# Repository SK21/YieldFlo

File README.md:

# YieldFlo

YieldFlo is a combine yield and moisture monitoring system that works alongside [AgOpenGPS](https://github.com/AgOpenGPS-Official/AgOpenGPS). A Windows desktop app records yield rate, moisture, and GPS position continuously while harvesting, and produces spatial yield maps and job reports — paired with open-source hardware that mounts on the combine's clean-grain elevator.

## How it works

- **YieldFlo module** (ESP32 or STM32F1 firmware) reads an optical grain-flow sensor on the clean-grain elevator, an optional capacitance moisture sensor, and an optional RPM sensor, then streams live readings to the PC over WiFi UDP, wired Ethernet UDP, or CAN bus.
- **AgOpenGPS** supplies GPS position and section on/off state over UDP on the same network.
- **YieldFlo (PC app)** combines both streams in real time, calculates yield, stores every point to a local SQLite database, renders a live color-coded yield map, and generates per-job reports and CSV exports.

## Repository layout

| Folder | Contents |
|---|---|
| [`YieldFlo/`](YieldFlo) | Main Windows Forms application (.NET) — the PC-side app |
| [`YieldFloApp/`](YieldFloApp) | Deployed/runnable build output (exe + resources) |
| [`Modules/ESP32/YieldFlo_ESP32`](Modules/ESP32/YieldFlo_ESP32) | Module firmware for ESP32 — WiFi/Ethernet/CAN, web-portal configuration, OTA updates |
| [`Modules/STM32F1/YieldFlo_STM32F1`](Modules/STM32F1/YieldFlo_STM32F1) | CAN-only module firmware for STM32F103 ("Blue Pill") — compile-time settings, no wireless |
| [`PCBs/YF1`](PCBs/YF1) | KiCad design for the main module board (sensor conditioning, CAN transceiver, etc.) |
| [`PCBs/Moisture1`](PCBs/Moisture1) | KiCad design for the moisture daughter board (ADS1115 + OEM capacitance sensor interface) |
| [`Tools/SensorSim`](Tools/SensorSim) | Arduino-based signal generator for bench-testing module firmware without a combine |
| [`ModuleSimulator/`](ModuleSimulator) | Windows app that emulates a module over the network, for testing the PC app without hardware |

Each `Modules/` folder has its own README with build instructions, pinouts, and protocol details — see the links above.

## Getting started

1. Extract a [release](../../releases) (or build `YieldFlo.sln`) and run `YieldFlo.exe` — no installer needed. Requires Windows 10/11 and .NET Framework 4.8.
2. Flash a module (ESP32 or STM32F1 — see the module READMEs) and wire it to the elevator/moisture sensors.
3. Run AgOpenGPS on the same PC or network.
4. In YieldFlo: set units, profile, crop, and header, then start a job.

Full instructions are in the in-app user manual (`Help` button, or [`YieldFlo/Help/YieldFlo User Manual.md`](YieldFlo/Help/YieldFlo%20User%20Manual.md)).

### Rebuilding the manual

`YieldFlo/Help/` holds the manual as `.md`, `.html` and `.pdf`. All three ship, so all three have to be kept in step — the `.md` and `.html` are edited by hand, and the `.pdf` is printed from the `.html` by headless Edge:

```
"C:\Program Files (x86)\Microsoft\Edge\Application\msedge.exe" ^
  --headless=new --disable-gpu --no-pdf-header-footer ^
  --print-to-pdf="YieldFlo User Manual.pdf" ^
  "file:///F:/path/to/YieldFlo/Help/YieldFlo User Manual.html"
```

`--no-pdf-header-footer` is what keeps the browser's own URL and page numbers off the pages. The HTML carries its own print CSS for page breaks, so nothing else needs setting. Chrome works identically — the PDF is produced by Chromium's Skia backend either way.

The build copies `Help/**` into `YieldFloApp/Help/`; that copy is output, not a second source to edit.

## Features

- Live main-screen gauges: yield rate, moisture, sensor status, area/total/average, work rate
- Color-coded live yield map (GMap.NET) with heading-up rotation and coverage tracking
- Profiles, crops, headers, and fields — reusable per-combine/per-crop configuration
- Two-point yield and moisture calibration workflows
- Job history with reports and CSV export (RateController-compatible)
- Imperial and metric units throughout
- Multi-language UI (English, German, French, Dutch, Polish, Hungarian, Lithuanian, Russian)
- CAN or WiFi/Ethernet module communication, selectable per install

## License

GPL-3.0 — see [`LICENSE`](LICENSE).

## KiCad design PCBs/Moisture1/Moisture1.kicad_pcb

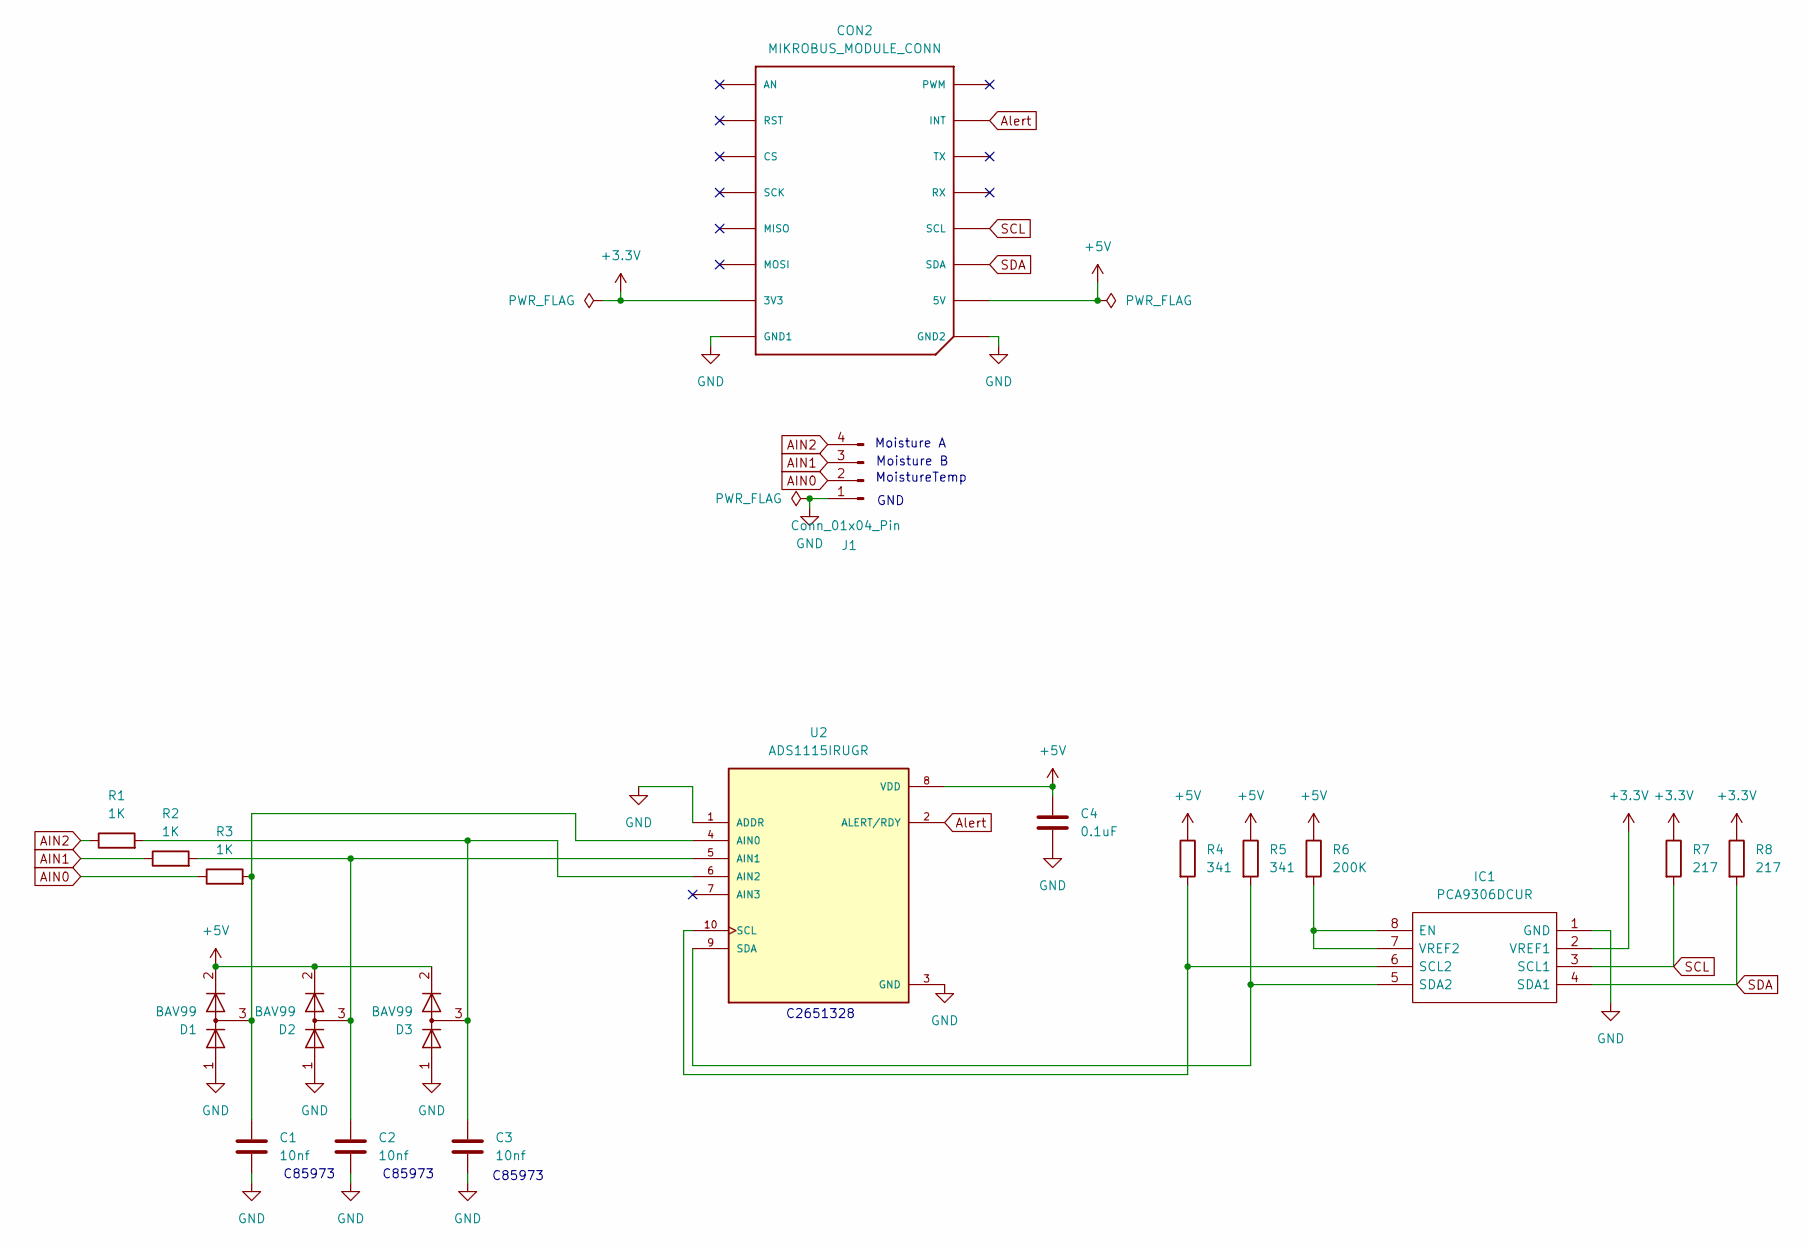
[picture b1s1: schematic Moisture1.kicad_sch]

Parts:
C1, C2, C3: 10nf; C_0603_1608Metric
C4: 0.1uF; C_0603_1608Metric
CON2: MIKROBUS_MODULE_CONN
D1, D2, D3: BAV99; SOT-23
IC1: PCA9306DCUR; Mouser Part Number 595-PCA9306DCUR
J1: Conn_01x04_Pin; PinHeader_1x04_P2.54mm_Vertical
R1, R2, R3: 1K; R_0603_1608Metric
R4, R5: 341; R_0603_1608Metric
R6: 200K; R_0603_1608Metric
R7, R8: 217; R_0603_1608Metric
U2: ADS1115IRUGR; IC_ADS1115IRUGR

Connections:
+3.3V: CON2.P7 (3V3), IC1.2 (VREF1), R7.1, R8.1
+5V: C4.1, CON2.P10 (5V), D1.2 (A), D2.2 (A), D3.2 (A), R4.1, R5.1, R6.1, U2.8 (VDD)
AIN0: J1.2, R3.1
AIN1: J1.3, R2.1
AIN2: J1.4, R1.1
Alert: CON2.P15 (INT), U2.2 (ALERT/RDY)
GND: C1.2, C2.2, C3.2, C4.2, CON2.P8 (GND1), CON2.P9 (GND2), D1.1 (K), D2.1 (K), D3.1 (K), IC1.1 (GND), J1.1, U2.1 (ADDR), U2.3 (GND)
unnamed: IC1.7 (VREF2), IC1.8 (EN), R6.2
unnamed: IC1.6 (SCL2), R4.2, U2.10 (SCL)
unnamed: IC1.5 (SDA2), R5.2, U2.9 (SDA)
unnamed: C1.1, D1.3 (K), R3.2, U2.4 (AIN0)
unnamed: C2.1, D2.3 (K), R2.2, U2.5 (AIN1)
unnamed: C3.1, D3.3 (K), R1.2, U2.6 (AIN2)
SCL: CON2.P12 (SCL), IC1.3 (SCL1), R7.2
SDA: CON2.P11 (SDA), IC1.4 (SDA1), R8.2

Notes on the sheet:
C85973
GND
C2651328
MoistureTemp
Moisture B
Moisture A

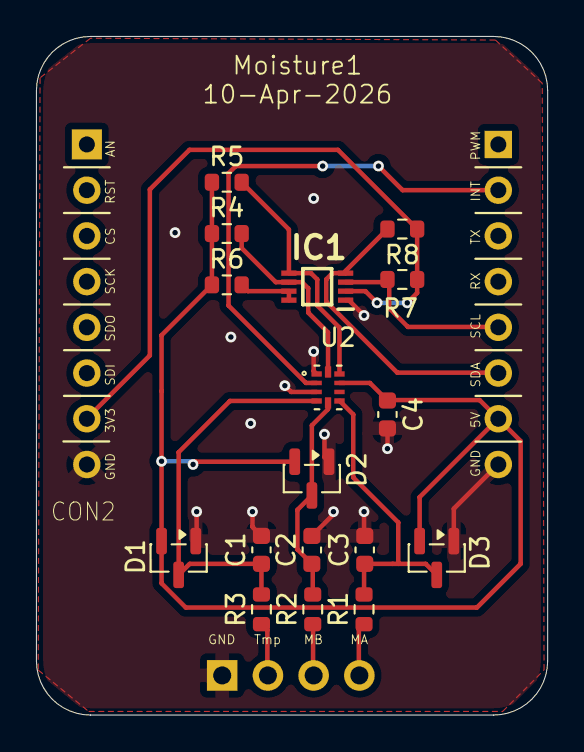
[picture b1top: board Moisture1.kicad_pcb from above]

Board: 2 copper layers, 28.4 x 37.7 mm, 19 parts (1 on the bottom side), 15 nets.

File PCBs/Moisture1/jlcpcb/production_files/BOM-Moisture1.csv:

Comment,Designator,Footprint,LCSC,Quantity
0.1uF,C4,C_0603_1608Metric,C14663,1
10nf,"C1,C2,C3",C_0603_1608Metric,C389113,3
1K,"R1,R2,R3",R_0603_1608Metric,C21190,3
200K,R6,R_0603_1608Metric,C25811,1
217,"R7,R8",R_0603_1608Metric,C2930075,2
341,"R4,R5",R_0603_1608Metric,C23138,2
ADS1115IRUGR,U2,IC_ADS1115IRUGR,C2651328,1
BAV99,"D1,D2,D3",SOT-23,C2500,3
PCA9306DCUR,IC1,PCA9306DCUR,C33196,1
MIKROBUS_MODULE_CONN,CON2,MIKROBUS_MODULE_CONN,,1
Conn_01x04_Pin,J1,PinHeader_1x04_P2.54mm_Vertical,,1

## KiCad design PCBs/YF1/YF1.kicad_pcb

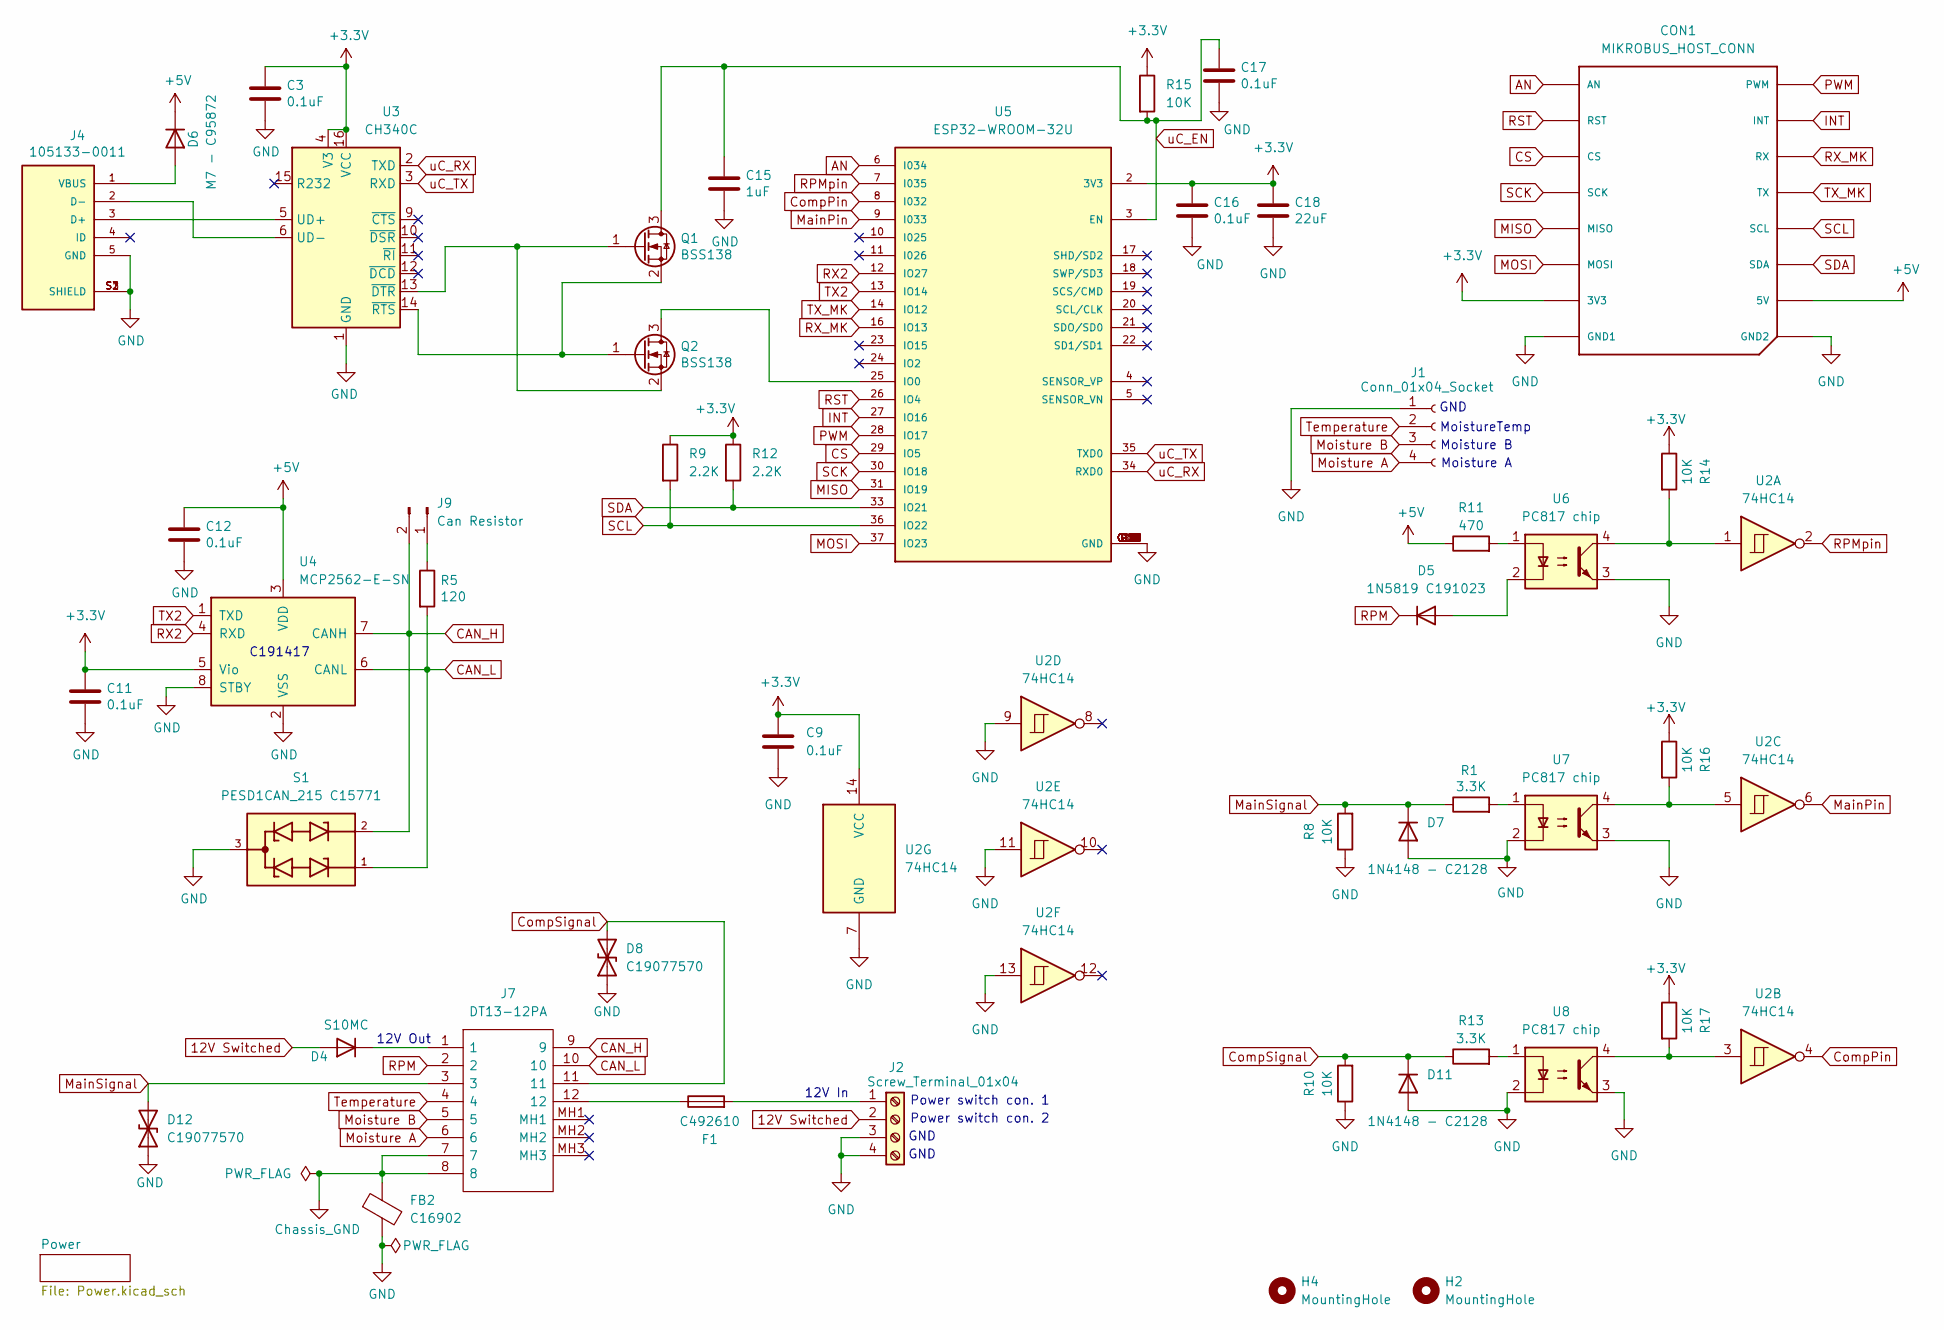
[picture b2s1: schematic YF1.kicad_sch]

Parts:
C3, C9, C11, C12, C16, C17: 0.1uF; C_0603_1608Metric
C15: 1uF; C_0603_1608Metric
C18: 22uF; C_0603_1608Metric
CON1: MIKROBUS_HOST_CONN
D4: S10MC; D_SMC_larger_pads
D5: 1N5819 C191023; 1N5819
D6: M7 - C95872; DO-214AC
D7, D11: 1N4148 - C2128; D_SOD-323
D8, D12: C19077570; D_SMB
F1: C492610; Fuse_Holder_C492610
FB2: C16902; D_1206_3216Metric
H2, H4: MountingHole; MountingHole_4.3mm_M4
J1: Conn_01x04_Socket; PinSocket_1x04_P2.54mm_Vertical
J2: Screw_Terminal_01x04; TerminalBlock_Phoenix_PT-1,5-4-5.0-H_1x04_P5.00mm_Horizontal
J4: 105133-0011; MOLEX_105133-0011; PARTREV C
J7: DT13-12PA; DT1312PA; Manufacturer_Part_Number DT13-12PA; Mouser Part Number 571-DT13-12PA
J9: Can Resistor; PinHeader_1x02_P2.54mm_Vertical
Q1, Q2: BSS138; SOT-23
R1, R13: 3.3K; R_0603_1608Metric
R5: 120; R_0603_1608Metric
R8, R10, R14, R15, R16, R17: 10K; R_0603_1608Metric
R9, R12: 2.2K; R_0603_1608Metric
R11: 470; R_0603_1608Metric
S1: PESD1CAN_215 C15771; DIO_PESD1CAN_215
U2: 74HC14; SOIC-14_3.9x8.7mm_P1.27mm
U3: CH340C; SOIC-16_3.9x9.9mm_P1.27mm
U4: MCP2562-E-SN; SOIC-8_3.9x4.9mm_P1.27mm
U5: ESP32-WROOM-32U; XCVR_ESP32-WROOM-32U; PARTREV V1.9
U6, U7, U8: PC817 chip; SMD-4_4.6x7.62mm_P2.54mm

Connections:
12V Switched: D4.2 (A), J2.2; also elsewhere on the board
+3.3V: C3.1, C9.1, C11.1, C16.1, C18.1, CON1.P7 (3V3), R9.1, R12.1, R14.1, R15.1, R16.1, R17.1, U2.14 (VCC), U3.4 (V3), U3.16 (VCC), U4.5 (Vio), U5.2 (3V3); also elsewhere on the board
+5V: C12.1, CON1.P10 (5V), D6.1 (K), R11.1, U4.3 (VDD); also elsewhere on the board
AN: CON1.P1 (AN), U5.6 (I034)
CAN_H: J7.9, J9.2, S1.2, U4.7 (CANH)
CAN_L: J7.10, R5.2, S1.1, U4.6 (CANL)
CS: CON1.P3 (CS), U5.29 (IO5)
Chassis_GND: FB2.1, J7.7, J7.8
CompPin: U2.4, U5.8 (I032)
CompSignal: D8.2 (A2), D11.1 (K), J7.11, R10.2, R13.1
GND: C3.2, C9.2, C11.2, C12.2, C15.2, C16.2, C17.2, C18.2, CON1.P8 (GND1), CON1.P9 (GND2), D7.2 (A), D8.1 (A1), D11.2 (A), D12.1 (A1), FB2.2, J1.1, J2.3, J2.4, J4.5 (GND), J4.S1 (SHIELD), J4.S2 (SHIELD), J4.S3 (SHIELD), R8.1, R10.1, S1.3, U2.7 (GND), U2.9, U2.11, U2.13, U3.1 (GND), U4.2 (VSS), U4.8 (STBY), U5.1 (GND), U5.15 (GND), U5.38 (GND), U5.G.1 (GND), U5.G.2 (GND), U5.G.4 (GND), U5.G.5 (GND), U5.G.6 (GND), U5.G.7 (GND), U5.G.8 (GND), U5.G.9 (GND), U5.G.10 (GND), U5.G.11 (GND), U5.G.12 (GND), U5.G.13 (GND), U5.G.14 (GND), U5.G.15 (GND), U5.G.16 (GND), U5.G.17 (GND), U5.G.18 (GND), U5.G.19 (GND), U5.G.20 (GND), U5.G.21 (GND), U5.G.22 (GND), U6.3, U7.2, U7.3, U8.2, U8.3; also elsewhere on the board
INT: CON1.P15 (INT), U5.27 (IO16)
MISO: CON1.P5 (MISO), U5.31 (IO19)
MOSI: CON1.P6 (MOSI), U5.37 (IO23)
MainPin: U2.6, U5.9 (I033)
MainSignal: D7.1 (K), D12.2 (A2), J7.3, R1.1, R8.2
Moisture A: J1.4, J7.6
Moisture B: J1.3, J7.5
unnamed: D4.1 (K), J7.1
unnamed: D5.2 (A), U6.2
unnamed: D6.2 (A), J4.1 (VBUS)
unnamed: F1.1, J7.12
unnamed: F1.2, J2.1
unnamed: J4.3 (D+), U3.5 (UD+)
unnamed: J4.2 (D-), U3.6 (UD-)
unnamed: J9.1, R5.1
unnamed: Q1.1 (G), Q2.2 (S), U3.13 (~DTR)
unnamed: Q1.2 (S), Q2.1 (G), U3.14 (~RTS)
unnamed: Q2.3 (D), U5.25 (IO0)
unnamed: R1.2, U7.1
unnamed: R11.2, U6.1
unnamed: R13.2, U8.1
unnamed: R14.2, U2.1, U6.4
unnamed: R16.2, U2.5, U7.4
unnamed: R17.2, U2.3, U8.4
PWM: CON1.P16 (PWM), U5.28 (IO17)
RPM: D5.1 (K), J7.2
RPMpin: U2.2, U5.7 (I035)
RST: CON1.P2 (RST), U5.26 (IO4)
RX2: U4.4 (RXD), U5.12 (IO27)
RX_MK: CON1.P14 (RX), U5.16 (IO13)
SCK: CON1.P4 (SCK), U5.30 (IO18)
SCL: CON1.P12 (SCL), R9.2, U5.36 (IO22)
SDA: CON1.P11 (SDA), R12.2, U5.33 (IO21)
TX2: U4.1 (TXD), U5.13 (IO14)
TX_MK: CON1.P13 (TX), U5.14 (IO12)
Temperature: J1.2, J7.4
uC_EN: C15.1, C17.1, Q1.3 (D), R15.2, U5.3 (EN)
uC_RX: U3.2 (TXD), U5.34 (RXD0)
uC_TX: U3.3 (RXD), U5.35 (TXD0)

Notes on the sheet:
Moisture A
12V Out
GND
MoistureTemp
12V In
Power switch con. 1
Power switch con. 2
C191417
Moisture B

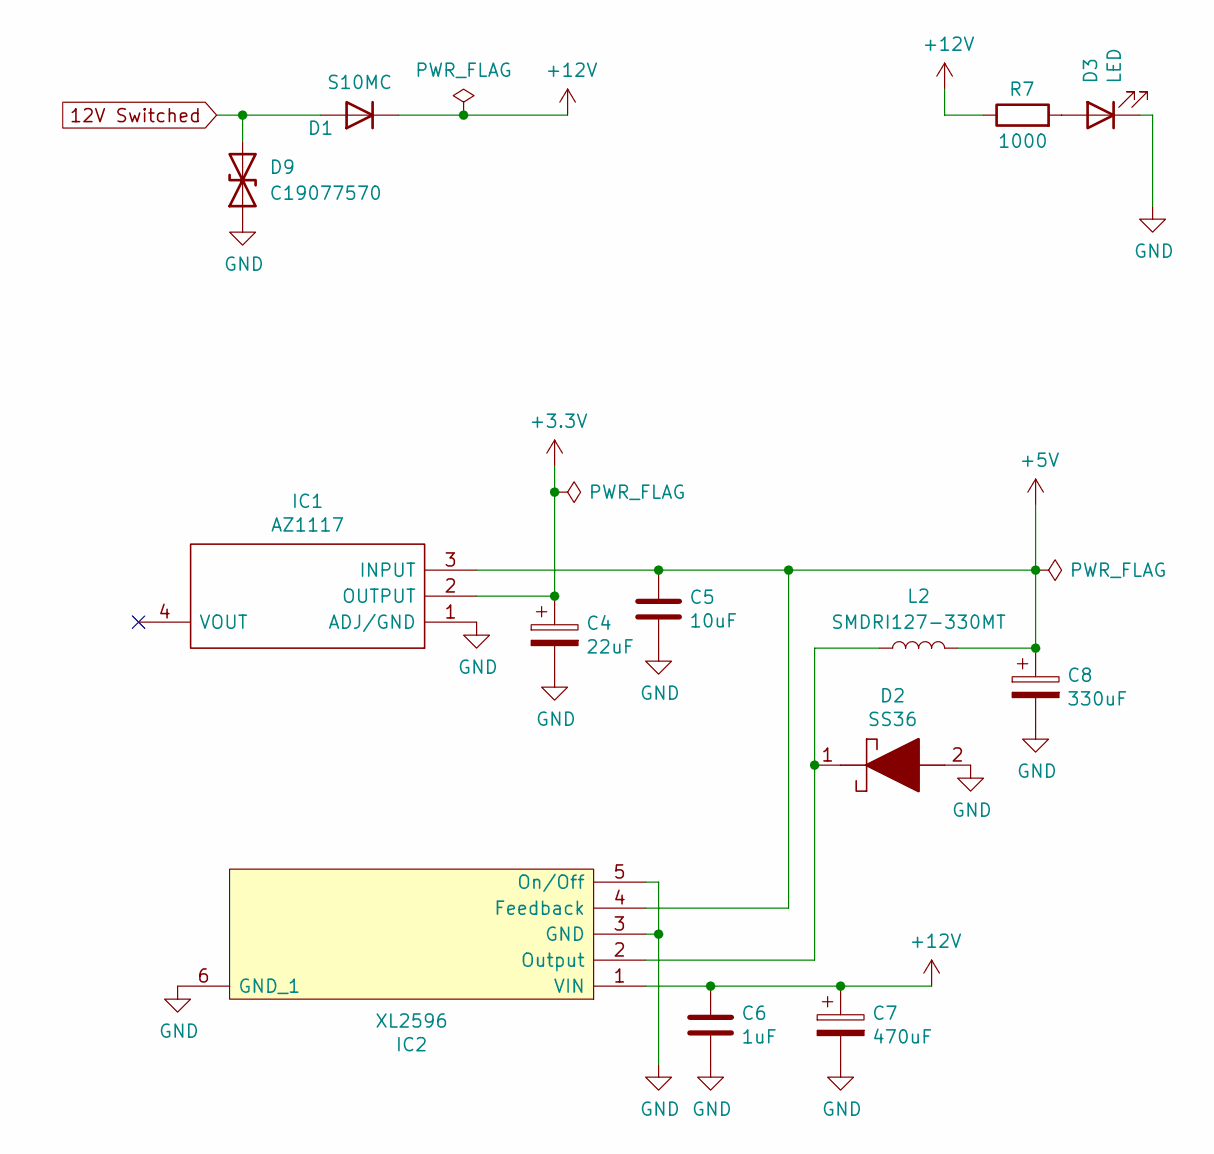
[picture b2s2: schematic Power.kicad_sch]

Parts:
C4: 22uF; C_0603_1608Metric
C5: 10uF; C_0603_1608Metric
C6: 1uF; C_0603_1608Metric
C7: 470uF; CP_Elec_10x10.5
C8: 330uF; CP_Elec_10x10.5
D1: S10MC; D_SMC_larger_pads
D2: SS36; SMA(DO-214AC)
D3: LED; LED_0805_2012Metric
D9: C19077570; D_SMB
IC1: AZ1117; SOT-223
IC2: XL2596; TO263-5L
L2: SMDRI127-330MT; TMPA1265SP-101MN-D
R7: 1000; R_0603_1608Metric

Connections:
12V Switched: D1.2 (A), D9.2 (A2); also elsewhere on the board
+3.3V: C4.1, IC1.2 (OUTPUT); also elsewhere on the board
+5V: C5.1, C8.1, IC1.3 (INPUT), IC2.4 (Feedback), L2.2; also elsewhere on the board
+12V: C6.1, C7.1, D1.1 (K), IC2.1 (VIN), R7.1
GND: C4.2, C5.2, C6.2, C7.2, C8.2, D2.2, D3.1 (K), D9.1 (A1), IC1.1 (ADJ/GND), IC2.3 (GND), IC2.5 (On/Off), IC2.6 (GND_1); also elsewhere on the board
unnamed: D3.2 (A), R7.2
unnamed: D2.1, IC2.2 (Output), L2.1

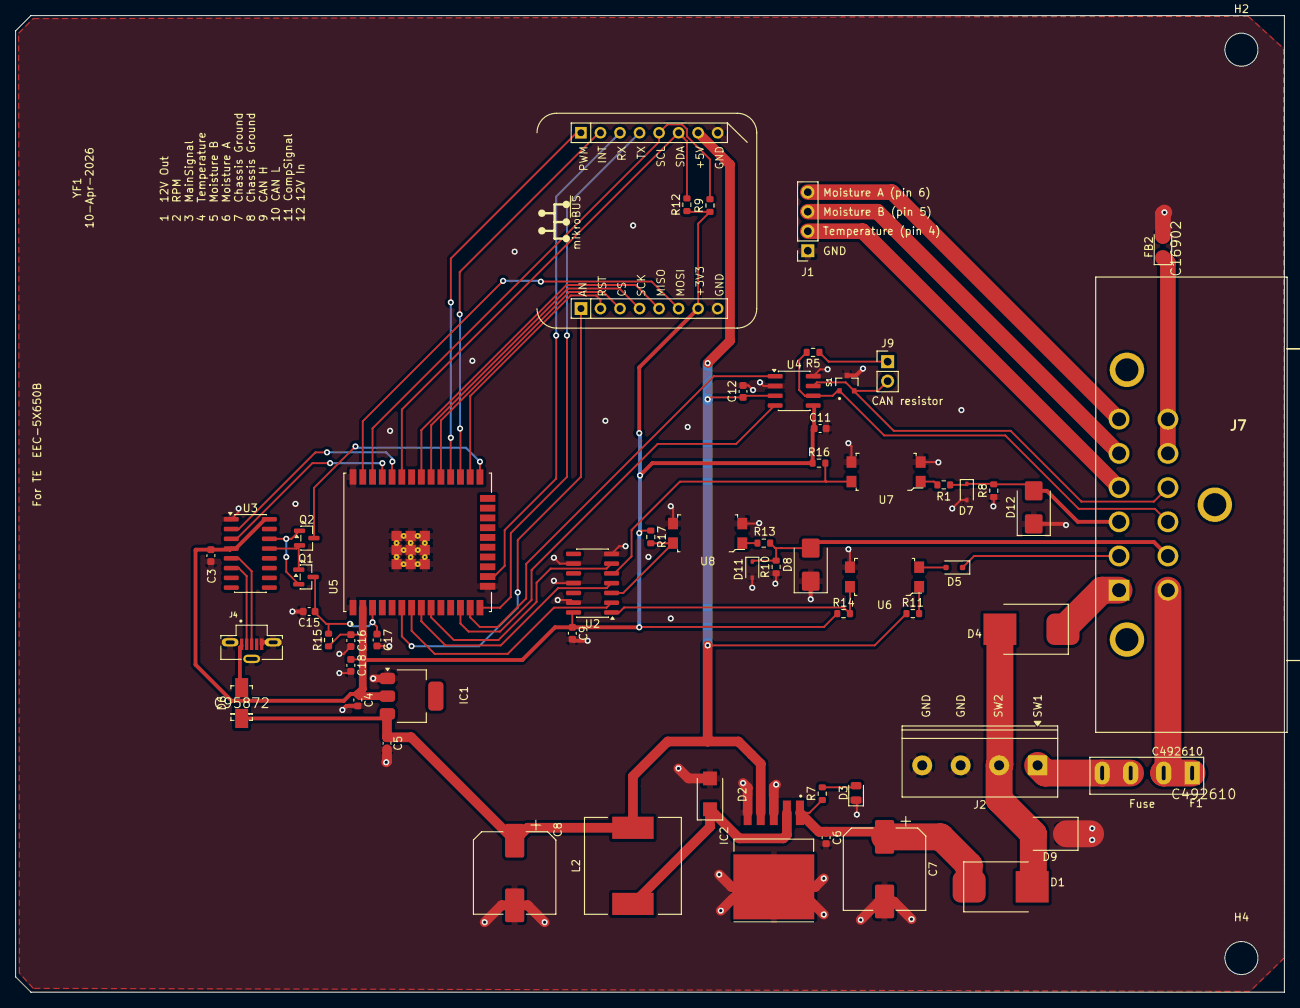
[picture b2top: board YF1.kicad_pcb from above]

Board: 2 copper layers, 165.0 x 127.0 mm, 60 parts (0 on the bottom side), 53 nets.

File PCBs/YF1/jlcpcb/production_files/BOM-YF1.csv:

Comment,Designator,Footprint,LCSC,Quantity
0.1uF,"C11,C12,C16,C17,C3,C9",C_0603_1608Metric,C14663,6
1000,R7,R_0603_1608Metric,C21190,1
105133-0011,J4,MOLEX_105133-0011,C586226,1
10K,"R10,R14,R15,R16,R17,R8",R_0603_1608Metric,C25804,6
10uF,C5,C_0603_1608Metric,C96446,1
120,R5,R_0603_1608Metric,C22787,1
1N4148 - C2128,"D11,D7",D_SOD-323,C2128,2
1N5819  C191023,D5,1N5819,C191023,1
1uF,"C15,C6",C_0603_1608Metric,C5199872,2
2.2K,"R12,R9",R_0603_1608Metric,C4190,2
22uF,"C18,C4",C_0603_1608Metric,C59461,2
3.3K,"R1,R13",R_0603_1608Metric,C2907023,2
330uF,C8,CP_Elec_10x10.5,C3032175,1
470,R11,R_0603_1608Metric,C114669,1
470uF,C7,CP_Elec_10x10.5,C2992611,1
74HC14,U2,SOIC-14_3.9x8.7mm_P1.27mm,C5605,1
AZ1117,IC1,SOT-223,C92102,1
BSS138,"Q1,Q2",SOT-23,C255592,2
C16902,FB2,D_1206_3216Metric,C16902,1
C19077570,"D12,D8,D9",D_SMB,C19077570,3
C492610,F1,Fuse_Holder_C492610,C492610,1
CH340C,U3,SOIC-16_3.9x9.9mm_P1.27mm,C84681,1
Can Resistor,J9,PinHeader_1x02_P2.54mm_Vertical,C7494857,1
Conn_01x04_Socket,J1,PinSocket_1x04_P2.54mm_Vertical,C2718488,1
ESP32-WROOM-32U,U5,XCVR_ESP32-WROOM-32U,C701344,1
LED,D3,LED_0805_2012Metric,C84256,1
M7 - C95872,D6,DO-214AC,C95872,1
MCP2562-E-SN,U4,SOIC-8_3.9x4.9mm_P1.27mm,C53609,1
PC817 chip,"U6,U7,U8",SMD-4_4.6x7.62mm_P2.54mm,C66405,3
PESD1CAN_215  C15771,S1,DIO_PESD1CAN_215,C15771,1
S10MC,"D1,D4",D_SMC_larger_pads,C169472,2
SMDRI127-330MT,L2,TMPA1265SP-101MN-D,C9400,1
SS36,D2,SMA(DO-214AC),C2903825,1
Screw_Terminal_01x04,J2,"TerminalBlock_Phoenix_PT-1,5-4-5.0-H_1x04_P5.00mm_Horizontal",C717432,1
XL2596,IC2,TO263-5L,C74190,1

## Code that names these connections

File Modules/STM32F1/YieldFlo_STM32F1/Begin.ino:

void DoSetup()
{
	uint8_t ErrorCount = 0;
	Serial.begin(38400);
	delay(2000);
	Serial.println();
	Serial.println();
	Serial.println(InoDescription);
	Serial.println();

	// version
	uint16_t yr = InoID % 10 + 2020;
	uint16_t rest = InoID / 10;
	uint8_t mn = rest % 100;
	uint16_t dy = rest / 100;

	String fwVer;
	if (mn <= 12 && dy <= 31)
	{
		fwVer = "Firmware Version: v";
		fwVer += String(yr);
		fwVer += ".";
		if (mn < 10) fwVer += "0";
		fwVer += String(mn);
		fwVer += ".";
		if (dy < 10) fwVer += "0";
		fwVer += String(dy);
	}
	else
	{
		fwVer = "Firmware Version: invalid";
	}
	Serial.println(fwVer);

	Serial.print("Module ID: ");
	Serial.println(ModuleID);
	Serial.println("");

	CheckExtiConflicts();

	// I2C
	Wire.begin();			// I2C1 on pins SCL PB6, SDA PB7
	Wire.setClock(400000);	// Increase I2C data rate to 400kHz

	// ADS1115
	if (ADS1115Enabled)
	{
		Serial.print("Starting ADS1115 at address ");
		Serial.println(ADS1115_Address);
		while (!ADSfound)
		{
			Wire.beginTransmission(ADS1115_Address);
			Wire.write(0b00000000);	//Point to Conversion register
			Wire.endTransmission();
			ADSfound = (Wire.requestFrom(ADS1115_Address, 2) == 2);
			Serial.print(".");
			delay(500);
			if (ErrorCount++ > 10) break;
		}
		Serial.println("");
		if (ADSfound)
		{
			Serial.println("ADS1115 found.");
			Serial.println("");

			// Configure ALERT/RDY pin for conversion-ready mode:
			// Set Hi_thresh MSB=1 and Lo_thresh MSB=0 — this puts ALERT/RDY
			// into conversion-ready mode regardless of comparator settings.
			Wire.beginTransmission(ADS1115_Address);
			Wire.write(0x02);		// Hi_thresh register
			Wire.write(0x80);		// 0x8000 MSB
			Wire.write(0x00);
			Wire.endTransmission();

			Wire.beginTransmission(ADS1115_Address);
			Wire.write(0x03);		// Lo_thresh register
			Wire.write(0x00);		// 0x0000
			Wire.write(0x00);
			Wire.endTransmission();

			// Attach interrupt — ALERT/RDY is open-drain active-low
			pinMode(AlertPin, INPUT_PULLUP);
			attachInterrupt(digitalPinToInterrupt(AlertPin), onADSReady, FALLING);

			// Start first conversion — moisture (AIN0-AIN1 differential, PGA=±4.096V, 16 SPS)
			Wire.beginTransmission(ADS1115_Address);
			Wire.write(0x01);		// Config register
			Wire.write(0b10000011);	// OS=1, MUX=000 (AIN0-AIN1 diff), PGA=001 (4.096V), MODE=1
			Wire.write(0b00100000);	// DR=001 (16 SPS), COMP_QUE=00
			Wire.endTransmission();
		}
		else
		{
			Serial.println("ADS1115 not found.");
			Serial.println("ADS1115 disabled.");
			Serial.println("");
		}
	}

	// Optical sensor
	Serial.print("Starting optical sensor ... ");
	pinMode(MainPin, INPUT);
	attachInterrupt(digitalPinToInterrupt(MainPin), onSensorEdge, CHANGE);
	if (UseCompSignal)
	{
		pinMode(CompPin, INPUT);
		attachInterrupt(digitalPinToInterrupt(CompPin), onSensorEdge, CHANGE);
	}
	BeamBlocked = ((digitalRead(MainPin) == HIGH) == InvertSensor);	// PNP: HIGH = clear; NPN inverted
	LastEdgeUs = micros();
	SegStartUs = LastEdgeUs;
	Serial.println(UseCompSignal ? "OK (Main + Comp)." : "OK (Main only).");

	// Both flow channels run off this one edge stream — duty on PK1, paddle
	// events on PK3. The pitch is not used in either calculation; it is the
	// factor that turns the PK3 flow rate into a grain column speed in mm/s.
	Serial.println("Flow channels: duty (PK1 0x18FF00F8) + paddle events (PK3 0x18FF02F8).");
	Serial.print("Paddle pitch (display only): ");
	Serial.print(PaddlePitchMm);
	Serial.println(" mm");

	// Debug LED — active-low onboard LED on PC13 mirrors the beam state
	if (DebugLED)
	{
		pinMode(LedPin, OUTPUT);
		digitalWrite(LedPin, BeamBlocked ? LOW : HIGH);	// LOW = lit when blocked
	}

	// RPM sensor
	if (RPMEnabled)
	{
		Serial.print("Starting RPM sensor ... ");
		pinMode(RPMPin, INPUT);
		attachInterrupt(digitalPinToInterrupt(RPMPin), onRPMedge, RISING);
		LastRPMedgeUs = micros();
		Serial.println("OK.");
	}

	// CAN bus — bxCAN on PB8/PB9 via the Can.h register driver.
	// remap 2 = CAN_RX on PB8, CAN_TX on PB9. CANInit() configures the GPIO,
	// bit timing, accept-all filter, single-shot TX (NART) and automatic
	// Bus-Off recovery (ABOM), then leaves the controller in normal mode.
	// It returns false if the peripheral never reaches normal mode (usually
	// a wiring/transceiver fault or missing 120R termination).
	Serial.println("Starting CAN ...");
	if (CANInit(CAN_250KBPS, 2))
	{
		Serial.println("CAN started at 250kbps.");
	}
	else
	{
		Serial.println("CAN init FAILED — check transceiver, wiring and termination.");
	}

	Serial.println("");
	Serial.println("Finished setup.");
	Serial.println("");
}

// EXTI lines are shared across ports by pin ordinal (PA5 and PB5 both use
// EXTI5), and attachInterrupt() silently reassigns a line that is already
// taken — the earlier pin just stops interrupting. Warn loudly at boot if
// any two ENABLED interrupt pins clash.
void CheckExtiConflicts()
{
	uint32_t pins[4];
	const char* names[4];
	uint8_t n = 0;
	pins[n] = MainPin; names[n] = "MainPin"; n++;
	if (UseCompSignal)  { pins[n] = CompPin;  names[n] = "CompPin";  n++; }
	if (RPMEnabled)     { pins[n] = RPMPin;   names[n] = "RPMPin";   n++; }
	if (ADS1115Enabled) { pins[n] = AlertPin; names[n] = "AlertPin"; n++; }

	for (uint8_t i = 0; i < n; i++)
	{
		for (uint8_t j = i + 1; j < n; j++)
		{
			if (STM_PIN(digitalPinToPinName(pins[i])) == STM_PIN(digitalPinToPinName(pins[j])))
			{
				Serial.print("WARNING: EXTI conflict — ");
				Serial.print(names[i]);
				Serial.print(" and ");
				Serial.print(names[j]);
				Serial.println(" share one EXTI line; one of them will NOT interrupt.");
			}
		}
	}
}

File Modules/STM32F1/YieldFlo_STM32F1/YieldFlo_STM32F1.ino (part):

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// silently. Turn it on only after confirming Comp is actually connected.
const bool    UseCompSignal  = false; // true = Main + Comp noise rejection, false = Main only (e.g. FarmTrx tap, Comp not wired)
const bool    InvertSensor   = true;  // true = NPN (inverted logic — default for this port), false = PNP (HIGH = beam clear, FarmTrx)
const bool    RPMEnabled     = true;  // RPM sensor wired to RPMPin
const bool    ADS1115Enabled = true;  // Moisture1 daughter board present
const bool    DebugLED       = true;  // PC13 onboard LED mirrors beam-blocked state (lit = blocked)

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// warning if enabled interrupt pins clash. Flow.ino derives its fast-read
// PinNames from these constants automatically, so nothing else needs editing
// when a pin changes.
const uint32_t MainPin   = PB0;   // main signal from light sensor       (EXTI0)
const uint32_t CompPin   = PB1;   // complementary signal                (EXTI1)
const uint32_t RPMPin    = PB10;  // RPM sensor                          (EXTI10)
const uint32_t AlertPin  = PB5;   // ADS1115 ALERT/RDY, open-drain       (EXTI5)
const bool     UseAnalogFallback = false;  // native ADC moisture when no ADS1115
const uint32_t AnalogPin = PA0;   // fallback ADC input (only if enabled above)
const uint32_t LedPin    = PC13;  // onboard LED, active-low — lit when beam blocked (debug)
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uint32_t       FlowLast = FlowTime;   // blocked/clear µs since the last packet is counted
const uint16_t SendTimePK1 = 200;  // ms = 5 Hz  (main data packet)
uint32_t       SendLastPK1 = SendTimePK1;
const uint16_t SendTimePK2 = 1000; // ms = 1 Hz  (temperature packet)
uint32_t       SendLastPK2 = SendTimePK2;

void setup()
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
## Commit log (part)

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2026-03-17 initial draft
2026-03-18 fill out menu
2026-03-18 ui fixes
2026-03-18 fix form display
2026-03-18 resume job
2026-03-18 fix calibrate
2026-03-18 numpad
2026-03-19 keyboard, numpad
2026-03-19 fix ui errors
2026-03-20 ui update
2026-03-20 yield sim
2026-03-20 fix sim
2026-03-20 module design
2026-03-26 update module code
2026-03-27 can comm
2026-03-27 change can pins
2026-03-27 moisture cal
2026-03-27 moisture and temp cal
2026-03-27 remove unused comm byte
2026-03-27 update sim
2026-03-27 update main form
2026-03-28 fix keyboard, numpad
2026-03-28 yield maps
2026-03-28 change data csv export
2026-03-28 language translations
2026-03-29 user manual
2026-03-29 menu fixes
2026-03-29 job notes
2026-03-29 fix missing mini button on main form
2026-03-29 fix message display
2026-03-29 fix udp share
2026-03-29 esp32 web page
2026-03-29 update user manual
2026-05-01 add missing files
2026-05-01 display module ip
